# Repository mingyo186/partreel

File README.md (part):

# PartReel — open KiCad parts registry for humans & AI agents

**No login. No paywall. Machine-verified.** Every part ships as a bundle of
KiCad footprint (`.kicad_mod`) + symbol (`.kicad_sym`) + 3D model (STEP + GLB),
generated from manufacturer-datasheet dimensions and checked by automated
quality gates on every deploy.

**Site:** https://partreel.com · **API:** https://partreel.com/api/ ·
**MCP server:** `https://mcp.partreel.com/mcp` · **Agent guide:** https://partreel.com/agents/

## Why this exists

- The official KiCad library is excellent — use it when it has your part.
  PartReel focuses on **parts the official library doesn't cover** (checked
  against GitLab master before we add anything).
- Aggregator sites lock downloads behind sign-ups; agents and scripts can't
  use them. Everything here is a plain URL.
- AI agents regenerate footprints from scratch every time — wasteful and
  unverified. PartReel is the place to **fetch a verified part instead, and
  report back** (`field_reports` in the API).

## Provenance — verify us, don't trust us

Every part's API entry (`/api/v1/parts/<id>.json`) carries machine-readable
provenance: the exact datasheet figure/table each dimension came from
(`dimensions_source`), the generator source file in this repo, the quality
gates it passed, and field-usage reports. Gates run in CI on every push and
**block deployment on failure** — see [`.github/workflows/deploy.yml`](.github/workflows/deploy.yml).

| Gate | Checks |
|---|---|
| `validate_kicad.py` | s-expression structure, pads, layers, pin-1 |
| KLC drawing rules | silk 0.12 / fab 0.10 + pin-1 chamfer / courtyard 0.05 |
| `check_overlap.py` | no overlapping text in previews |
| `check_render.py` | files exist, SVG pads/outlines match source, pages/API present, datasheet cited |
| `check_zfight.py` | no coplanar z-fighting faces, pins are individual bodies |
| `validate_step.py` | STEP solids pass FreeCAD kernel isValid |

## For AI agents

- Static JSON API, no auth, no rate limit: [`/api/v1/parts.json`](https://partreel.com/api/v1/parts.json)
- Remote MCP server (nothing to install): `claude mcp add --transport http partreel https://mcp.partreel.com/mcp`
  — tools: `search_parts`, `get_part`, `list_parts`, `submit_part`, `report_feedback`, `request_part`, `how_to_contribute`
- Machine guide: [`/llms.txt`](https://partreel.com/llms.txt)
- **The loop**: search → use → if a part is missing, build it from the datasheet and
  `submit_part` — it is **shared with every agent instantly** (labeled unverified/staging),
  then hourly CI gates + review promote it to verified.
- `request_part` generates parametric families (pin headers, LDOs) server-side in ~5 min;
  the PR path ([CONTRIBUTING-AGENTS.md](CONTRIBUTING-AGENTS.md)) remains for 3D models and edits.

## Repository layout

```
library/                 part assets (CC-BY-4.0): .kicad_mod / .kicad_sym / .step / .glb / meta.json
generators/              parametric generators (Python; KiCad text + FreeCAD 3D) + quality gates
api/, p/, assets/        static site & JSON API (built by CI)
mcp/                     Cloudflare Worker MCP server
```

## License

- **Code** (generators, site): [MIT](LICENSE)
- **Part assets** (library/): [CC-BY-4.0](library/LICENSE)

Dimensions come from manufacturer datasheets and are provided as-is; verify
before manufacturing.

## Credits

Bug reports are contributions. Reporters whose feedback led to a fix are
recorded in [CREDITS.md](CREDITS.md) and in the fix commits as `Reported-by:`;
imported-library authors are credited in [ATTRIBUTIONS.md](ATTRIBUTIONS.md).

## Parts index

<!-- PARTS:BEGIN -->
Currently **18258 parts**, all machine-verified (structure, KLC drawing rules, render completeness, 3D coplanar/merged-pin checks, STEP kernel) with datasheet-cited dimensions.

### connector (4330)

| Part | MPN | Manufacturer | Files |
|---|---|---|---|
| [004500 (CERN library)](https://partreel.com/p/cern_erni_004500/) | `004500` | ERNI | [cern_erni_004500](library/connector/cern/cern_erni_004500) |
| [02 01 160 2101 (CERN library)](https://partreel.com/p/cern_harting_02_01_160_2101/) | `02 01 160 2101` | HARTING | [cern_harting_02_01_160_2101](library/connector/cern/cern_harting_02_01_160_2101) |
| [02 01 160 2102 (CERN library)](https://partreel.com/p/cern_harting_02_01_160_2102/) | `02 01 160 2102` | HARTING | [cern_harting_02_01_160_2102](library/connector/cern/cern_harting_02_01_160_2102) |
| [02 02 160 2201 (CERN library)](https://partreel.com/p/cern_harting_02_02_160_2201/) | `02 02 160 2201` | HARTING | [cern_harting_02_02_160_2201](library/connector/cern/cern_harting_02_02_160_2201) |
| [02 02 160 2301 (CERN library)](https://partreel.com/p/cern_harting_02_02_160_2301/) | `02 02 160 2301` | HARTING | [cern_harting_02_02_160_2301](library/connector/cern/cern_harting_02_02_160_2301) |
| [02 04 160 1101 (CERN library)](https://partreel.com/p/cern_harting_02_04_160_1101/) | `02 04 160 1101` | HARTING | [cern_harting_02_04_160_1101](library/connector/cern/cern_harting_02_04_160_1101) |
| [02 07 160 1101 (CERN library)](https://partreel.com/p/cern_harting_02_07_160_1101/) | `02 07 160 1101` | HARTING | [cern_harting_02_07_160_1101](library/connector/cern/cern_harting_02_07_160_1101) |
| [031-6575 (CERN library)](https://partreel.com/p/cern_amphenol_031_6575/) | `031-6575` | AMPHENOL-RF | [cern_amphenol_031_6575](library/connector/cern/cern_amphenol_031_6575) |
| [054392 (CERN library)](https://partreel.com/p/cern_erni_054392/) | `054392` | ERNI | [cern_erni_054392](library/connector/cern/cern_erni_054392) |
| [054546 (CERN library)](https://partreel.com/p/cern_erni_054546/) | `054546` | ERNI | [cern_erni_054546](library/connector/cern/cern_erni_054546) |
| [054594 (CERN library)](https://partreel.com/p/cern_erni_054594/) | `054594` | ERNI | [cern_erni_054594](library/connector/cern/cern_erni_054594) |
| [054595 (CERN library)](https://partreel.com/p/cern_erni_054595/) | `054595` | ERNI | [cern_erni_054595](library/connector/cern/cern_erni_054595) |
| [054596 (CERN library)](https://partreel.com/p/cern_erni_054596/) | `054596` | ERNI | [cern_erni_054596](library/connector/cern/cern_erni_054596) |
| [063197 (CERN library)](https://partreel.com/p/cern_erni_063197/) | `063197` | ERNI | [cern_erni_063197](library/connector/cern/cern_erni_063197) |
| [063209 (CERN library)](https://partreel.com/p/cern_erni_063209/) | `063209` | ERNI | [cern_erni_063209](library/connector/cern/cern_erni_063209) |
| [063210 (CERN library)](https://partreel.com/p/cern_erni_063210/) | `063210` | ERNI | [cern_erni_063210](library/connector/cern/cern_erni_063210) |
| [064317 (CERN library)](https://partreel.com/p/cern_erni_064317/) | `064317` | ERNI | [cern_erni_064317](library/connector/cern/cern_erni_064317) |
| [064318 (CERN library)](https://partreel.com/p/cern_erni_064318/) | `064318` | ERNI | [cern_erni_064318](library/connector/cern/cern_erni_064318) |
| [064321 (CERN library)](https://partreel.com/p/cern_erni_064321/) | `064321` | ERNI | [cern_erni_064321](library/connector/cern/cern_erni_064321) |
| [09 02 164 2921 (CERN library)](https://partreel.com/p/cern_harting_09_02_164_2921/) | `09 02 164 2921` | HARTING | [cern_harting_09_02_164_2921](library/connector/cern/cern_harting_09_02_164_2921) |
| [09 02 264 6825 (CERN library)](https://partreel.com/p/cern_harting_09_02_264_6825/) | `09 02 264 6825` | HARTING | [cern_harting_09_02_264_6825](library/connector/cern/cern_harting_09_02_264_6825) |
| [09 02 264 6850 (CERN library)](https://partreel.com/p/cern_harting_09_02_264_6850/) | `09 02 264 6850` | HARTING | [cern_harting_09_02_264_6850](library/connector/cern/cern_harting_09_02_264_6850) |
| [09 03 000 6104 (CERN library)](https://partreel.com/p/cern_harting_09_03_000_6104/) | `09 03 000 6104` | HARTING | [cern_harting_09_03_000_6104](library/connector/cern/cern_harting_09_03_000_6104) |
| [09 03 000 6110 (CERN library)](https://partreel.com/p/cern_harting_09_03_000_6110/) | `09 03 000 6110` | HARTING | [cern_harting_09_03_000_6110](library/connector/cern/cern_harting_09_03_000_6110) |
| [09 03 000 6162 (CERN library)](https://partreel.com/p/cern_harting_09_03_000_6162/) | `09 03 000 6162` | HARTING | [cern_harting_09_03_000_6162](library/connector/cern/cern_harting_09_03_000_6162) |
| [09 03 000 6182 (CERN library)](https://partreel.com/p/cern_harting_09_03_000_6182/) | `09 03 000 6182` | HARTING | [cern_harting_09_03_000_6182](library/connector/cern/cern_harting_09_03_000_6182) |
| [09 03 000 6225 (CERN library)](https://partreel.com/p/cern_harting_09_03_000_6225/) | `09 03 000 6225` | HARTING | [cern_harting_09_03_000_6225](library/connector/cern/cern_harting_09_03_000_6225) |
| [09 03 000 6262 (CERN library)](https://partreel.com/p/cern_harting_09_03_000_6262/) | `09 03 000 6262` | HARTING | [cern_harting_09_03_000_6262](library/connector/cern/cern_harting_09_03_000_6262) |
| [09 03 000 6265 (CERN library)](https://partreel.com/p/cern_harting_09_03_000_6265/) | `09 03 000 6265` | HARTING | [cern_harting_09_03_000_6265](library/connector/cern/cern_harting_09_03_000_6265) |
| [09 03 124 6901 (CERN library)](https://partreel.com/p/cern_harting_09_03_124_6901/) | `09 03 124 6901` | HARTING | [cern_harting_09_03_124_6901](library/connector/cern/cern_harting_09_03_124_6901) |
| [09 03 142 6901 (CERN library)](https://partreel.com/p/cern_harting_09_03_142_6901/) | `09 03 142 6901` | HARTING | [cern_harting_09_03_142_6901](library/connector/cern/cern_harting_09_03_142_6901) |
| [09 03 160 6901 (CERN library)](https://partreel.com/p/cern_harting_09_03_160_6901/) | `09 03 160 6901` | HARTING | [cern_harting_09_03_160_6901](library/connector/cern/cern_harting_09_03_160_6901) |
| [09 03 164 2921 (CERN library)](https://partreel.com/p/cern_harting_09_03_164_2921/) | `09 03 164 2921` | HARTING | [cern_harting_09_03_164_2921](library/connector/cern/cern_harting_09_03_164_2921) |
| [09 03 164 6921 (CERN library)](https://partreel.com/p/cern_harting_09_03_164_6921/) | `09 03 164 6921` | HARTING | [cern_harting_09_03_164_6921](library/connector/cern/cern_harting_09_03_164_6921) |
| [09 03 164 6922 (CERN library)](https://partreel.com/p/cern_harting_09_03_164_6922/) | `09 03 164 6922` | HARTING | [cern_harting_09_03_164_6922](library/connector/cern/cern_harting_09_03_164_6922) |
| [09 03 164 6951 (CERN library)](https://partreel.com/p/cern_harting_09_03_164_6951/) | `09 03 164 6951` | HARTING | [cern_harting_09_03_164_6951](library/connector/cern/cern_harting_09_03_164_6951) |
| [09 03 178 7901 (CERN library)](https://partreel.com/p/cern_harting_09_03_178_7901/) | `09 03 178 7901` | HARTING | [cern_harting_09_03_178_7901](library/connector/cern/cern_harting_09_03_178_7901) |
| [09 03 196 2921 (CERN library)](https://partreel.com/p/cern_harting_09_03_196_2921/) | `09 03 196 2921` | HARTING | [cern_harting_09_03_196_2921](library/connector/cern/cern_harting_09_03_196_2921) |
| [09 03 196 6921 (CERN library)](https://partreel.com/p/cern_harting_09_03_196_6921/) | `09 03 196 6921` | HARTING | [cern_harting_09_03_196_6921](library/connector/cern/cern_harting_09_03_196_6921) |
| [09 03 224 6805 (CERN library)](https://partreel.com/p/cern_harting_09_03_224_6805/) | `09 03 224 6805` | HARTING | [cern_harting_09_03_224_6805](library/connector/cern/cern_harting_09_03_224_6805) |
| [09 03 224 6830 (CERN library)](https://partreel.com/p/cern_harting_09_03_224_6830/) | `09 03 224 6830` | HARTING | [cern_harting_09_03_224_6830](library/connector/cern/cern_harting_09_03_224_6830) |
| [09 03 224 6864 (CERN library)](https://partreel.com/p/cern_harting_09_03_224_6864/) | `09 03 224 6864` | HARTING | [cern_harting_09_03_224_6864](library/connector/cern/cern_harting_09_03_224_6864) |
| [09 03 224 6864 (CERN library)](https://partreel.com/p/cern_harting_09_03_224_6864_a/) | `09 03 224 6864` | HARTING | [cern_harting_09_03_224_6864_a](library/connector/cern/cern_harting_09_03_224_6864_a) |
| [09 03 232 6825 (CERN library)](https://partreel.com/p/cern_harting_09_03_232_6825/) | `09 03 232 6825` | HARTING | [cern_harting_09_03_232_6825](library/connector/cern/cern_harting_09_03_232_6825) |
| [09 03 232 6850 (CERN library)](https://partreel.com/p/cern_harting_09_03_232_6850/) | `09 03 232 6850` | HARTING | [cern_harting_09_03_232_6850](library/connector/cern/cern_harting_09_03_232_6850) |
| [09 03 242 6805 (CERN library)](https://partreel.com/p/cern_harting_09_03_242_6805/) | `09 03 242 6805` | HARTING | [cern_harting_09_03_242_6805](library/connector/cern/cern_harting_09_03_242_6805) |
| [09 03 242 6805 (CERN library)](https://partreel.com/p/cern_harting_09_03_242_6805_a/) | `09 03 242 6805` | HARTING | [cern_harting_09_03_242_6805_a](library/connector/cern/cern_harting_09_03_242_6805_a) |
| [09 03 260 6804 (CERN library)](https://partreel.com/p/cern_harting_09_03_260_6804/) | `09 03 260 6804` | HARTING | [cern_harting_09_03_260_6804](library/connector/cern/cern_harting_09_03_260_6804) |
| [09 03 264 6825 (CERN library)](https://partreel.com/p/cern_harting_09_03_264_6825/) | `09 03 264 6825` | HARTING | [cern_harting_09_03_264_6825](library/connector/cern/cern_harting_09_03_264_6825) |
| [09 03 264 6850 (CERN library)](https://partreel.com/p/cern_harting_09_03_264_6850/) | `09 03 264 6850` | HARTING | [cern_harting_09_03_264_6850](library/connector/cern/cern_harting_09_03_264_6850) |
| [09 03 278 6804 (CERN library)](https://partreel.com/p/cern_harting_09_03_278_6804/) | `09 03 278 6804` | HARTING | [cern_harting_09_03_278_6804](library/connector/cern/cern_harting_09_03_278_6804) |
| [09 03 296 2825 (CERN library)](https://partreel.com/p/cern_harting_09_03_296_2825/) | `09 03 296 2825` | HARTING | [cern_harting_09_03_296_2825](library/connector/cern/cern_harting_09_03_296_2825) |
| [09 03 296 2850 (CERN library)](https://partreel.com/p/cern_harting_09_03_296_2850/) | `09 03 296 2850` | HARTING | [cern_harting_09_03_296_2850](library/connector/cern/cern_harting_09_03_296_2850) |
| [09 03 296 6824 (CERN library)](https://partreel.com/p/cern_harting_09_03_296_6824/) | `09 03 296 6824` | HARTING | [cern_harting_09_03_296_6824](library/connector/cern/cern_harting_09_03_296_6824) |
| [09 03 296 6825 (CERN library)](https://partreel.com/p/cern_harting_09_03_296_6825/) | `09 03 296 6825` | HARTING | [cern_harting_09_03_296_6825](library/connector/cern/cern_harting_09_03_296_6825) |
| [09 03 296 6850 (CERN library)](https://partreel.com/p/cern_harting_09_03_296_6850/) | `09 03 296 6850` | HARTING | [cern_harting_09_03_296_6850](library/connector/cern/cern_harting_09_03_296_6850) |
| [09 03 296 6861 (CERN library)](https://partreel.com/p/cern_harting_09_03_296_6861/) | `09 03 296 6861` | HARTING | [cern_harting_09_03_296_6861](library/connector/cern/cern_harting_09_03_296_6861) |
| [09 03 478 6864 (CERN library)](https://partreel.com/p/cern_harting_09_03_478_6864/) | `09 03 478 6864` | HARTING | [cern_harting_09_03_478_6864](library/connector/cern/cern_harting_09_03_478_6864) |
| [09 03 696 6921 (CERN library)](https://partreel.com/p/cern_harting_09_03_696_6921/) | `09 03 696 6921` | HARTING | [cern_harting_09_03_696_6921](library/connector/cern/cern_harting_09_03_696_6921) |
| [09 03 796 6825 (CERN library)](https://partreel.com/p/cern_harting_09_03_796_6825/) | `09 03 796 6825` | HARTING | [cern_harting_09_03_796_6825](library/connector/cern/cern_harting_09_03_796_6825) |
| [09 03 796 6850 (CERN library)](https://partreel.com/p/cern_harting_09_03_796_6850/) | `09 03 796 6850` | HARTING | [cern_harting_09_03_796_6850](library/connector/cern/cern_harting_09_03_796_6850) |
| [09 04 132 2921 (CERN library)](https://partreel.com/p/cern_harting_09_04_132_2921/) | `09 04 132 2921` | HARTING | [cern_harting_09_04_132_2921](library/connector/cern/cern_harting_09_04_132_2921) |
| [09 04 132 6921 (CERN library)](https://partreel.com/p/cern_harting_09_04_132_6921/) | `09 04 132 6921` | HARTING | [cern_harting_09_04_132_6921](library/connector/cern/cern_harting_09_04_132_6921) |
| [09 04 232 6826 (CERN library)](https://partreel.com/p/cern_harting_09_04_232_6826/) | `09 04 232 6826` | HARTING | [cern_harting_09_04_232_6826](library/connector/cern/cern_harting_09_04_232_6826) |
| [09 04 232 6831 (CERN library)](https://partreel.com/p/cern_harting_09_04_232_6831/) | `09 04 232 6831` | HARTING | [cern_harting_09_04_232_6831](library/connector/cern/cern_harting_09_04_232_6831) |
| [09 05 148 2931 (CERN library)](https://partreel.com/p/cern_harting_09_05_148_2931/) | `09 05 148 2931` | HARTING | [cern_harting_09_05_148_2931](library/connector/cern/cern_harting_09_05_148_2931) |
| [09 05 248 6831 (CERN library)](https://partreel.com/p/cern_harting_09_05_248_6831/) | `09 05 248 6831` | HARTING | [cern_harting_09_05_248_6831](library/connector/cern/cern_harting_09_05_248_6831) |
| [09 06 031 2921 (CERN library)](https://partreel.com/p/cern_harting_09_06_031_2921/) | `09 06 031 2921` | HARTING | [cern_harting_09_06_031_2921](library/connector/cern/cern_harting_09_06_031_2921) |
| [09 06 048 2905 (CERN library)](https://partreel.com/p/cern_harting_09_06_048_2905/) | `09 06 048 2905` | HARTING | [cern_harting_09_06_048_2905](library/connector/cern/cern_harting_09_06_048_2905) |
| [09 06 115 2911 (CERN library)](https://partreel.com/p/cern_harting_09_06_115_2911/) | `09 06 115 2911` | HARTING | [cern_harting_09_06_115_2911](library/connector/cern/cern_harting_09_06_115_2911) |
| [09 06 131 6922 (CERN library)](https://partreel.com/p/cern_harting_09_06_131_6922/) | `09 06 131 6922` | HARTING | [cern_harting_09_06_131_6922](library/connector/cern/cern_harting_09_06_131_6922) |
| [09 06 131 6924 (CERN library)](https://partreel.com/p/cern_harting_09_06_131_6924/) | `09 06 131 6924` | HARTING | [cern_harting_09_06_131_6924](library/connector/cern/cern_harting_09_06_131_6924) |
| [09 06 132 6931 (CERN library)](https://partreel.com/p/cern_harting_09_06_132_6931/) | `09 06 132 6931` | HARTING | [cern_harting_09_06_132_6931](library/connector/cern/cern_harting_09_06_132_6931) |
| [09 06 148 2901 222 (CERN library)](https://partreel.com/p/cern_harting_09_06_148_2901_222/) | `09 06 148 2901 222` | HARTING | [cern_harting_09_06_148_2901_222](library/connector/cern/cern_harting_09_06_148_2901_222) |
| [09 06 148 6901 (CERN library)](https://partreel.com/p/cern_harting_09_06_148_6901/) | `09 06 148 6901` | HARTING | [cern_harting_09_06_148_6901](library/connector/cern/cern_harting_09_06_148_6901) |
| [09 06 203 2811 (CERN library)](https://partreel.com/p/cern_harting_09_06_203_2811/) | `09 06 203 2811` | HARTING | [cern_harting_09_06_203_2811](library/connector/cern/cern_harting_09_06_203_2811) |
| [09 06 215 2811 (CERN library)](https://partreel.com/p/cern_harting_09_06_215_2811/) | `09 06 215 2811` | HARTING | [cern_harting_09_06_215_2811](library/connector/cern/cern_harting_09_06_215_2811) |
| [09 06 215 2821 (CERN library)](https://partreel.com/p/cern_harting_09_06_215_2821/) | `09 06 215 2821` | HARTING | [cern_harting_09_06_215_2821](library/connector/cern/cern_harting_09_06_215_2821) |
| [09 06 215 2854 (CERN library)](https://partreel.com/p/cern_harting_09_06_215_2854/) | `09 06 215 2854` | HARTING | [cern_harting_09_06_215_2854](library/connector/cern/cern_harting_09_06_215_2854) |
| [09 06 215 2856 (CERN library)](https://partreel.com/p/cern_harting_09_06_215_2856/) | `09 06 215 2856` | HARTING | [cern_harting_09_06_215_2856](library/connector/cern/cern_harting_09_06_215_2856) |
| [09 06 231 2881 (CERN library)](https://partreel.com/p/cern_harting_09_06_231_2881/) | `09 06 231 2881` | HARTING | [cern_harting_09_06_231_2881](library/connector/cern/cern_harting_09_06_231_2881) |
| [09 06 231 6822 (CERN library)](https://partreel.com/p/cern_harting_09_06_231_6822/) | `09 06 231 6822` | HARTING | [cern_harting_09_06_231_6822](library/connector/cern/cern_harting_09_06_231_6822) |
| [09 06 231 6822 (CERN library)](https://partreel.com/p/cern_harting_09_06_231_6822_a/) | `09 06 231 6822` | HARTING | [cern_harting_09_06_231_6822_a](library/connector/cern/cern_harting_09_06_231_6822_a) |
| [09 06 248 6826 (CERN library)](https://partreel.com/p/cern_harting_09_06_248_6826/) | `09 06 248 6826` | HARTING | [cern_harting_09_06_248_6826](library/connector/cern/cern_harting_09_06_248_6826) |
| [09 06 248 6832 (CERN library)](https://partreel.com/p/cern_harting_09_06_248_6832/) | `09 06 248 6832` | HARTING | [cern_harting_09_06_248_6832](library/connector/cern/cern_harting_09_06_248_6832) |
| [09 06 248 6834 (CERN library)](https://partreel.com/p/cern_harting_09_06_248_6834/) | `09 06 248 6834` | HARTING | [cern_harting_09_06_248_6834](library/connector/cern/cern_harting_09_06_248_6834) |
| [09 06 248 6836 (CERN library)](https://partreel.com/p/cern_harting_09_06_248_6836/) | `09 06 248 6836` | HARTING | [cern_harting_09_06_248_6836](library/connector/cern/cern_harting_09_06_248_6836) |
| [09 06 248 7833 (CERN library)](https://partreel.com/p/cern_harting_09_06_248_7833/) | `09 06 248 7833` | HARTING | [cern_harting_09_06_248_7833](library/connector/cern/cern_harting_09_06_248_7833) |
| [09 12 000 9905 (CERN library)](https://partreel.com/p/cern_harting_09_12_000_9905/) | `09 12 000 9905` | HARTING | [cern_harting_09_12_000_9905](library/connector/cern/cern_harting_09_12_000_9905) |
| [09 12 000 9905 (CERN library)](https://partreel.com/p/cern_harting_09_12_000_9905_alt/) | `09 12 000 9905` | HARTING | [cern_harting_09_12_000_9905_alt](library/connector/cern/cern_harting_09_12_000_9905_alt) |
| [09 12 000 9908 (CERN library)](https://partreel.com/p/cern_harting_09_12_000_9908/) | `09 12 000 9908` | HARTING | [cern_harting_09_12_000_9908](library/connector/cern/cern_harting_09_12_000_9908) |
| [09 12 012 9901 (CERN library)](https://partreel.com/p/cern_harting_09_12_012_9901/) | `09 12 012 9901` | HARTING | [cern_harting_09_12_012_9901](library/connector/cern/cern_harting_09_12_012_9901) |
| [09 16 000 9908 (CERN library)](https://partreel.com/p/cern_harting_09_16_000_9908/) | `09 16 000 9908` | HARTING | [cern_harting_09_16_000_9908](library/connector/cern/cern_harting_09_16_000_9908) |
| [09 16 000 9918 (CERN library)](https://partreel.com/p/cern_harting_09_16_000_9918/) | `09 16 000 9918` | HARTING | [cern_harting_09_16_000_9918](library/connector/cern/cern_harting_09_16_000_9918) |
| [09 16 000 9918 (CERN library)](https://partreel.com/p/cern_harting_09_16_000_9918_alt/) | `09 16 000 9918` | HARTING | [cern_harting_09_16_000_9918_alt](library/connector/cern/cern_harting_09_16_000_9918_alt) |
| [09 18 516 6324 (CERN library)](https://partreel.com/p/cern_harting_09_18_516_6324/) | `09 18 516 6324` | HARTING | [cern_harting_09_18_516_6324](library/connector/cern/cern_harting_09_18_516_6324) |
| [09 18 516 6324 (CERN library)](https://partreel.com/p/cern_harting_09_18_516_6324_alt/) | `09 18 516 6324` | HARTING | [cern_harting_09_18_516_6324_alt](library/connector/cern/cern_harting_09_18_516_6324_alt) |
| [09 19 564 6824 (CERN library)](https://partreel.com/p/cern_harting_09_19_564_6824/) | `09 19 564 6824` | HARTING | [cern_harting_09_19_564_6824](library/connector/cern/cern_harting_09_19_564_6824) |
| [09 19 564 6824 (CERN library)](https://partreel.com/p/cern_harting_09_19_564_6824_alt/) | `09 19 564 6824` | HARTING | [cern_harting_09_19_564_6824_alt](library/connector/cern/cern_harting_09_19_564_6824_alt) |
| [09 22 116 6921 (CERN library)](https://partreel.com/p/cern_harting_09_22_116_6921/) | `09 22 116 6921` | HARTING | [cern_harting_09_22_116_6921](library/connector/cern/cern_harting_09_22_116_6921) |
| [09 22 132 6921 (CERN library)](https://partreel.com/p/cern_harting_09_22_132_6921/) | `09 22 132 6921` | HARTING | [cern_harting_09_22_132_6921](library/connector/cern/cern_harting_09_22_132_6921) |
| [09 22 232 6825 (CERN library)](https://partreel.com/p/cern_harting_09_22_232_6825/) | `09 22 232 6825` | HARTING | [cern_harting_09_22_232_6825](library/connector/cern/cern_harting_09_22_232_6825) |
| [09 22 232 6850 (CERN library)](https://partreel.com/p/cern_harting_09_22_232_6850/) | `09 22 232 6850` | HARTING | [cern_harting_09_22_232_6850](library/connector/cern/cern_harting_09_22_232_6850) |
| [09 23 116 6931 (CERN library)](https://partreel.com/p/cern_harting_09_23_116_6931/) | `09 23 116 6931` | HARTING | [cern_harting_09_23_116_6931](library/connector/cern/cern_harting_09_23_116_6931) |
| [09 23 116 6931 (CERN library)](https://partreel.com/p/cern_harting_09_23_116_6931_alt/) | `09 23 116 6931` | HARTING | [cern_harting_09_23_116_6931_alt](library/connector/cern/cern_harting_09_23_116_6931_alt) |
| [09 23 132 7921 (CERN library)](https://partreel.com/p/cern_harting_09_23_132_7921/) | `09 23 132 7921` | HARTING | [cern_harting_09_23_132_7921](library/connector/cern/cern_harting_09_23_132_7921) |
| [09 23 148 6921 (CERN library)](https://partreel.com/p/cern_harting_09_23_148_6921/) | `09 23 148 6921` | HARTING | [cern_harting_09_23_148_6921](library/connector/cern/cern_harting_09_23_148_6921) |
| [09 23 148 6951 (CERN library)](https://partreel.com/p/cern_harting_09_23_148_6951/) | `09 23 148 6951` | HARTING | [cern_harting_09_23_148_6951](library/connector/cern/cern_harting_09_23_148_6951) |
| [09 23 248 6824 (CERN library)](https://partreel.com/p/cern_harting_09_23_248_6824/) | `09 23 248 6824` | HARTING | [cern_harting_09_23_248_6824](library/connector/cern/cern_harting_09_23_248_6824) |
| [09 23 248 6850 (CERN library)](https://partreel.com/p/cern_harting_09_23_248_6850/) | `09 23 248 6850` | HARTING | [cern_harting_09_23_248_6850](library/connector/cern/cern_harting_09_23_248_6850) |
| [09 23 248 6866 (CERN library)](https://partreel.com/p/cern_harting_09_23_248_6866/) | `09 23 248 6866` | HARTING | [cern_harting_09_23_248_6866](library/connector/cern/cern_harting_09_23_248_6866) |
| [09 25 120 6921 (CERN library)](https://partreel.com/p/cern_harting_09_25_120_6921/) | `09 25 120 6921` | HARTING | [cern_harting_09_25_120_6921](library/connector/cern/cern_harting_09_25_120_6921) |
| [09 25 130 6921 (CERN library)](https://partreel.com/p/cern_harting_09_25_130_6921/) | `09 25 130 6921` | HARTING | [cern_harting_09_25_130_6921](library/connector/cern/cern_harting_09_25_130_6921) |
| [09 25 130 6922 (CERN library)](https://partreel.com/p/cern_harting_09_25_130_6922/) | `09 25 130 6922` | HARTING | [cern_harting_09_25_130_6922](library/connector/cern/cern_harting_09_25_130_6922) |
| [09 25 230 6824 (CERN library)](https://partreel.com/p/cern_harting_09_25_230_6824/) | `09 25 230 6824` | HARTING | [cern_harting_09_25_230_6824](library/connector/cern/cern_harting_09_25_230_6824) |
| [09 25 230 6850 (CERN library)](https://partreel.com/p/cern_harting_09_25_230_6850/) | `09 25 230 6850` | HARTING | [cern_harting_09_25_230_6850](library/connector/cern/cern_harting_09_25_230_6850) |
| [09 28 148 6519 (CERN library)](https://partreel.com/p/cern_harting_09_28_148_6519/) | `09 28 148 6519` | HARTING | [cern_harting_09_28_148_6519](library/connector/cern/cern_harting_09_28_148_6519) |
| [09 28 148 6902 (CERN library)](https://partreel.com/p/cern_harting_09_28_148_6902/) | `09 28 148 6902` | HARTING | [cern_harting_09_28_148_6902](library/connector/cern/cern_harting_09_28_148_6902) |
| [09 28 248 6801 (CERN library)](https://partreel.com/p/cern_harting_09_28_248_6801/) | `09 28 248 6801` | HARTING | [cern_harting_09_28_248_6801](library/connector/cern/cern_harting_09_28_248_6801) |
| [09 29 130 6904 (CERN library)](https://partreel.com/p/cern_harting_09_29_130_6904/) | `09 29 130 6904` | HARTING | [cern_harting_09_29_130_6904](library/connector/cern/cern_harting_09_29_130_6904) |
| [09 29 130 6904 (CERN library)](https://partreel.com/p/cern_harting_09_29_130_6904_reverse/) | `09 29 130 6904` | HARTING | [cern_harting_09_29_130_6904_reverse](library/connector/cern/cern_harting_09_29_130_6904_reverse) |
| [09 32 000 6295 (CERN library)](https://partreel.com/p/cern_harting_09_32_000_6295/) | `09 32 000 6295` | HARTING | [cern_harting_09_32_000_6295](library/connector/cern/cern_harting_09_32_000_6295) |
| [09 32 000 6295 (CERN library)](https://partreel.com/p/cern_harting_09_32_000_6295_alt/) | `09 32 000 6295` | HARTING | [cern_harting_09_32_000_6295_alt](library/connector/cern/cern_harting_09_32_000_6295_alt) |
| [09 33 000 9811 (CERN library)](https://partreel.com/p/cern_harting_09_33_000_9811/) | `09 33 000 9811` | HARTING | [cern_harting_09_33_000_9811](library/connector/cern/cern_harting_09_33_000_9811) |
| [09 33 000 9812 (CERN library)](https://partreel.com/p/cern_harting_09_33_000_9812/) | `09 33 000 9812` | HARTING | [cern_harting_09_33_000_9812](library/connector/cern/cern_harting_09_33_000_9812) |
| [09 33 000 9812 (CERN library)](https://partreel.com/p/cern_harting_09_33_000_9812_a/) | `09 33 000 9812` | HARTING | [cern_harting_09_33_000_9812_a](library/connector/cern/cern_harting_09_33_000_9812_a) |
| [09 33 000 9813 (CERN library)](https://partreel.com/p/cern_harting_09_33_000_9813/) | `09 33 000 9813` | HARTING | [cern_harting_09_33_000_9813](library/connector/cern/cern_harting_09_33_000_9813) |
| [09 33 000 9815 (CERN library)](https://partreel.com/p/cern_harting_09_33_000_9815/) | `09 33 000 9815` | HARTING | [cern_harting_09_33_000_9815](library/connector/cern/cern_harting_09_33_000_9815) |
| [09 33 000 9815 (CERN library)](https://partreel.com/p/cern_harting_09_33_000_9815_a/) | `09 33 000 9815` | HARTING | [cern_harting_09_33_000_9815_a](library/connector/cern/cern_harting_09_33_000_9815_a) |
| [09 33 000 9870 (CERN library)](https://partreel.com/p/cern_harting_09_33_000_9870/) | `09 33 000 9870` | HARTING | [cern_harting_09_33_000_9870](library/connector/cern/cern_harting_09_33_000_9870) |
| [09 33 000 9870 (CERN library)](https://partreel.com/p/cern_harting_09_33_000_9870_alt/) | `09 33 000 9870` | HARTING | [cern_harting_09_33_000_9870_alt](library/connector/cern/cern_harting_09_33_000_9870_alt) |
| [09 33 000 9871 (CERN library)](https://partreel.com/p/cern_harting_09_33_000_9871/) | `09 33 000 9871` | HARTING | [cern_harting_09_33_000_9871](library/connector/cern/cern_harting_09_33_000_9871) |
| [09 33 000 9871 (CERN library)](https://partreel.com/p/cern_harting_09_33_000_9871_alt/) | `09 33 000 9871` | HARTING | [cern_harting_09_33_000_9871_alt](library/connector/cern/cern_harting_09_33_000_9871_alt) |
| [09 33 000 9872 (CERN library)](https://partreel.com/p/cern_harting_09_33_000_9872/) | `09 33 000 9872` | HARTING | [cern_harting_09_33_000_9872](library/connector/cern/cern_harting_09_33_000_9872) |
| [09 33 000 9872 (CERN library)](https://partreel.com/p/cern_harting_09_33_000_9872_alt/) | `09 33 000 9872` | HARTING | [cern_harting_09_33_000_9872_alt](library/connector/cern/cern_harting_09_33_000_9872_alt) |
| [09 33 000 9873 (CERN library)](https://partreel.com/p/cern_harting_09_33_000_9873/) | `09 33 000 9873` | HARTING | [cern_harting_09_33_000_9873](library/connector/cern/cern_harting_09_33_000_9873) |
| [09 33 000 9880 (CERN library)](https://partreel.com/p/cern_harting_09_33_000_9880/) | `09 33 000 9880` | HARTING | [cern_harting_09_33_000_9880](library/connector/cern/cern_harting_09_33_000_9880) |
| [09 33 000 9880 (CERN library)](https://partreel.com/p/cern_harting_09_33_000_9880_alt/) | `09 33 000 9880` | HARTING | [cern_harting_09_33_000_9880_alt](library/connector/cern/cern_harting_09_33_000_9880_alt) |
| [09 33 000 9996 (CERN library)](https://partreel.com/p/cern_harting_09_33_000_9996/) | `09 33 000 9996` | HARTING | [cern_harting_09_33_000_9996](library/connector/cern/cern_harting_09_33_000_9996) |
| [09 45 281 2800 (CERN library)](https://partreel.com/p/cern_harting_09_45_281_2800/) | `09 45 281 2800` | HARTING | [cern_harting_09_45_281_2800](library/connector/cern/cern_harting_09_45_281_2800) |
| [09 45 281 2810 (CERN library)](https://partreel.com/p/cern_harting_09_45_281_2810/) | `09 45 281 2810` | HARTING | [cern_harting_09_45_281_2810](library/connector/cern/cern_harting_09_45_281_2810) |
| [09 46 500 3400 (CERN library)](https://partreel.com/p/cern_harting_09_46_500_3400/) | `09 46 500 3400` | HARTING | [cern_harting_09_46_500_3400](library/connector/cern/cern_harting_09_46_500_3400) |
| [09 46 500 4400 (CERN library)](https://partreel.com/p/cern_harting_09_46_500_4400/) | `09 46 500 4400` | HARTING | [cern_harting_09_46_500_4400](library/connector/cern/cern_harting_09_46_500_4400) |
| [09 46 500 4400 (CERN library)](https://partreel.com/p/cern_harting_09_46_500_4400_alt/) | `09 46 500 4400` | HARTING | [cern_harting_09_46_500_4400_alt](library/connector/cern/cern_harting_09_46_500_4400_alt) |
| [09 55 315 6612 741 (CERN library)](https://partreel.com/p/cern_harting_09_55_315_6612_741/) | `09 55 315 6612 741` | HARTING | [cern_harting_09_55_315_6612_741](library/connector/cern/cern_harting_09_55_315_6612_741) |
| [09 55 315 6612 741 (CERN library)](https://partreel.com/p/cern_harting_09_55_315_6612_741_alt/) | `09 55 315 6612 741` | HARTING | [cern_harting_09_55_315_6612_741_alt](library/connector/cern/cern_harting_09_55_315_6612_741_alt) |
| [09 56 151 5513 (CERN library)](https://partreel.com/p/cern_harting_09_56_151_5513/) | `09 56 151 5513` | HARTING | [cern_harting_09_56_151_5513](library/connector/cern/cern_harting_09_56_151_5513) |
| [09 56 151 5513 (CERN library)](https://partreel.com/p/cern_harting_09_56_151_5513_alt/) | `09 56 151 5513` | HARTING | [cern_harting_09_56_151_5513_alt](library/connector/cern/cern_harting_09_56_151_5513_alt) |
| [09 56 251 5512 (CERN library)](https://partreel.com/p/cern_harting_09_56_251_5512/) | `09 56 251 5512` | HARTING | [cern_harting_09_56_251_5512](library/connector/cern/cern_harting_09_56_251_5512) |
| [09 56 251 5512 (CERN library)](https://partreel.com/p/cern_harting_09_56_251_5512_alt/) | `09 56 251 5512` | HARTING | [cern_harting_09_56_251_5512_alt](library/connector/cern/cern_harting_09_56_251_5512_alt) |
| [09 56 251 7512 (CERN library)](https://partreel.com/p/cern_harting_09_56_251_7512/) | `09 56 251 7512` | HARTING | [cern_harting_09_56_251_7512](library/connector/cern/cern_harting_09_56_251_7512) |
| [09 56 251 7512 (CERN library)](https://partreel.com/p/cern_harting_09_56_251_7512_alt/) | `09 56 251 7512` | HARTING | [cern_harting_09_56_251_7512_alt](library/connector/cern/cern_harting_09_56_251_7512_alt) |
| [09 56 262 7812 (CERN library)](https://partreel.com/p/cern_harting_09_56_262_7812/) | `09 56 262 7812` | HARTING | [cern_harting_09_56_262_7812](library/connector/cern/cern_harting_09_56_262_7812) |
| [09 56 262 7812 (CERN library)](https://partreel.com/p/cern_harting_09_56_262_7812_alt/) | `09 56 262 7812` | HARTING | [cern_harting_09_56_262_7812_alt](library/connector/cern/cern_harting_09_56_262_7812_alt) |
| [09 56 351 5513 (CERN library)](https://partreel.com/p/cern_harting_09_56_351_5513/) | `09 56 351 5513` | HARTING | [cern_harting_09_56_351_5513](library/connector/cern/cern_harting_09_56_351_5513) |
| [09 56 351 5513 (CERN library)](https://partreel.com/p/cern_harting_09_56_351_5513_alt/) | `09 56 351 5513` | HARTING | [cern_harting_09_56_351_5513_alt](library/connector/cern/cern_harting_09_56_351_5513_alt) |
| [09 56 451 5512 (CERN library)](https://partreel.com/p/cern_harting_09_56_451_5512/) | `09 56 451 5512` | HARTING | [cern_harting_09_56_451_5512](library/connector/cern/cern_harting_09_56_451_5512) |
| [09 56 451 5512 (CERN library)](https://partreel.com/p/cern_harting_09_56_451_5512_alt/) | `09 56 451 5512` | HARTING | [cern_harting_09_56_451_5512_alt](library/connector/cern/cern_harting_09_56_451_5512_alt) |
| [09 56 461 5712 (CERN library)](https://partreel.com/p/cern_harting_09_56_461_5712/) | `09 56 461 5712` | HARTING | [cern_harting_09_56_461_5712](library/connector/cern/cern_harting_09_56_461_5712) |
| [09 56 461 5712 (CERN library)](https://partreel.com/p/cern_harting_09_56_461_5712_alt/) | `09 56 461 5712` | HARTING | [cern_harting_09_56_461_5712_alt](library/connector/cern/cern_harting_09_56_461_5712_alt) |
| [09 56 551 5512 (CERN library)](https://partreel.com/p/cern_harting_09_56_551_5512/) | `09 56 551 5512` | HARTING | [cern_harting_09_56_551_5512](library/connector/cern/cern_harting_09_56_551_5512) |
| [09 56 551 5512 (CERN library)](https://partreel.com/p/cern_harting_09_56_551_5512_alt/) | `09 56 551 5512` | HARTING | [cern_harting_09_56_551_5512_alt](library/connector/cern/cern_harting_09_56_551_5512_alt) |
| [09 56 551 7513 (CERN library)](https://partreel.com/p/cern_harting_09_56_551_7513/) | `09 56 551 7513` | HARTING | [cern_harting_09_56_551_7513](library/connector/cern/cern_harting_09_56_551_7513) |
| [09 56 551 7513 (CERN library)](https://partreel.com/p/cern_harting_09_56_551_7513_alt/) | `09 56 551 7513` | HARTING | [cern_harting_09_56_551_7513_alt](library/connector/cern/cern_harting_09_56_551_7513_alt) |
| [09 56 552 7613 (CERN library)](https://partreel.com/p/cern_harting_09_56_552_7613/) | `09 56 552 7613` | HARTING | [cern_harting_09_56_552_7613](library/connector/cern/cern_harting_09_56_552_7613) |
| [09 56 552 7613 (CERN library)](https://partreel.com/p/cern_harting_09_56_552_7613_alt/) | `09 56 552 7613` | HARTING | [cern_harting_09_56_552_7613_alt](library/connector/cern/cern_harting_09_56_552_7613_alt) |
| [09 56 561 7713 (CERN library)](https://partreel.com/p/cern_harting_09_56_561_7713/) | `09 56 561 7713` | HARTING | [cern_harting_09_56_561_7713](library/connector/cern/cern_harting_09_56_561_7713) |
| [09 56 561 7713 (CERN library)](https://partreel.com/p/cern_harting_09_56_561_7713_alt/) | `09 56 561 7713` | HARTING | [cern_harting_09_56_561_7713_alt](library/connector/cern/cern_harting_09_56_561_7713_alt) |
| [09 56 562 7813 (CERN library)](https://partreel.com/p/cern_harting_09_56_562_7813/) | `09 56 562 7813` | HARTING | [cern_harting_09_56_562_7813](library/connector/cern/cern_harting_09_56_562_7813) |
| [09 56 562 7813 (CERN library)](https://partreel.com/p/cern_harting_09_56_562_7813_alt/) | `09 56 562 7813` | HARTING | [cern_harting_09_56_562_7813_alt](library/connector/cern/cern_harting_09_56_562_7813_alt) |
| [09 65 162 6811 (CERN library)](https://partreel.com/p/cern_harting_09_65_162_6811/) | `09 65 162 6811` | HARTING | [cern_harting_09_65_162_6811](library/connector/cern/cern_harting_09_65_162_6811) |
| [09 65 162 6811 (CERN library)](https://partreel.com/p/cern_harting_09_65_162_6811_alt/) | `09 65 162 6811` | HARTING | [cern_harting_09_65_162_6811_alt](library/connector/cern/cern_harting_09_65_162_6811_alt) |
| [09 65 162 6812 (CERN library)](https://partreel.com/p/cern_harting_09_65_162_6812/) | `09 65 162 6812` | HARTING | [cern_harting_09_65_162_6812](library/connector/cern/cern_harting_09_65_162_6812) |
| [09 65 162 6812 (CERN library)](https://partreel.com/p/cern_harting_09_65_162_6812_alt/) | `09 65 162 6812` | HARTING | [cern_harting_09_65_162_6812_alt](library/connector/cern/cern_harting_09_65_162_6812_alt) |
| [09 65 262 6812 (CERN library)](https://partreel.com/p/cern_harting_09_65_262_6812/) | `09 65 262 6812` | HARTING | [cern_harting_09_65_262_6812](library/connector/cern/cern_harting_09_65_262_6812) |
| [09 65 262 6812 (CERN library)](https://partreel.com/p/cern_harting_09_65_262_6812_alt/) | `09 65 262 6812` | HARTING | [cern_harting_09_65_262_6812_alt](library/connector/cern/cern_harting_09_65_262_6812_alt) |
| [09 65 321 7701 (CERN library)](https://partreel.com/p/cern_harting_09_65_321_7701/) | `09 65 321 7701` | HARTING | [cern_harting_09_65_321_7701](library/connector/cern/cern_harting_09_65_321_7701) |
| [09 65 321 7701 (CERN library)](https://partreel.com/p/cern_harting_09_65_321_7701_alt/) | `09 65 321 7701` | HARTING | [cern_harting_09_65_321_7701_alt](library/connector/cern/cern_harting_09_65_321_7701_alt) |
| [09 65 361 6712 (CERN library)](https://partreel.com/p/cern_harting_09_65_361_6712/) | `09 65 361 6712` | HARTING | [cern_harting_09_65_361_6712](library/connector/cern/cern_harting_09_65_361_6712) |
| [09 65 361 6712 (CERN library)](https://partreel.com/p/cern_harting_09_65_361_6712_alt/) | `09 65 361 6712` | HARTING | [cern_harting_09_65_361_6712_alt](library/connector/cern/cern_harting_09_65_361_6712_alt) |
| [09 65 362 6812 (CERN library)](https://partreel.com/p/cern_harting_09_65_362_6812/) | `09 65 362 6812` | HARTING | [cern_harting_09_65_362_6812](library/connector/cern/cern_harting_09_65_362_6812) |
| [09 65 362 6812 (CERN library)](https://partreel.com/p/cern_harting_09_65_362_6812_alt/) | `09 65 362 6812` | HARTING | [cern_harting_09_65_362_6812_alt](library/connector/cern/cern_harting_09_65_362_6812_alt) |
| [09 65 421 7702 (CERN library)](https://partreel.com/p/cern_harting_09_65_421_7702/) | `09 65 421 7702` | HARTING | [cern_harting_09_65_421_7702](library/connector/cern/cern_harting_09_65_421_7702) |
| [09 65 421 7702 (CERN library)](https://partreel.com/p/cern_harting_09_65_421_7702_alt/) | `09 65 421 7702` | HARTING | [cern_harting_09_65_421_7702_alt](library/connector/cern/cern_harting_09_65_421_7702_alt) |
| [09 65 462 6812 (CERN library)](https://partreel.com/p/cern_harting_09_65_462_6812/) | `09 65 462 6812` | HARTING | [cern_harting_09_65_462_6812](library/connector/cern/cern_harting_09_65_462_6812) |
| [09 65 462 6812 (CERN library)](https://partreel.com/p/cern_harting_09_65_462_6812_alt/) | `09 65 462 6812` | HARTING | [cern_harting_09_65_462_6812_alt](library/connector/cern/cern_harting_09_65_462_6812_alt) |
| [09 66 111 7501 (CERN library)](https://partreel.com/p/cern_harting_09_66_111_7501/) | `09 66 111 7501` | HARTING | [cern_harting_09_66_111_7501](library/connector/cern/cern_harting_09_66_111_7501) |
| [09 66 111 7501 (CERN library)](https://partreel.com/p/cern_harting_09_66_111_7501_alt/) | `09 66 111 7501` | HARTING | [cern_harting_09_66_111_7501_alt](library/connector/cern/cern_harting_09_66_111_7501_alt) |
| [09 66 111 7502 (CERN library)](https://partreel.com/p/cern_harting_09_66_111_7502/) | `09 66 111 7502` | HARTING | [cern_harting_09_66_111_7502](library/connector/cern/cern_harting_09_66_111_7502) |
| [09 66 111 7502 (CERN library)](https://partreel.com/p/cern_harting_09_66_111_7502_alt/) | `09 66 111 7502` | HARTING | [cern_harting_09_66_111_7502_alt](library/connector/cern/cern_harting_09_66_111_7502_alt) |
| [09 66 152 6612 (CERN library)](https://partreel.com/p/cern_harting_09_66_152_6612/) | `09 66 152 6612` | HARTING | [cern_harting_09_66_152_6612](library/connector/cern/cern_harting_09_66_152_6612) |
| [09 66 152 6612 (CERN library)](https://partreel.com/p/cern_harting_09_66_152_6612_alt/) | `09 66 152 6612` | HARTING | [cern_harting_09_66_152_6612_alt](library/connector/cern/cern_harting_09_66_152_6612_alt) |
| [09 66 162 6817 (CERN library)](https://partreel.com/p/cern_harting_09_66_162_6817/) | `09 66 162 6817` | HARTING | [cern_harting_09_66_162_6817](library/connector/cern/cern_harting_09_66_162_6817) |
| [09 66 162 6817 (CERN library)](https://partreel.com/p/cern_harting_09_66_162_6817_alt/) | `09 66 162 6817` | HARTING | [cern_harting_09_66_162_6817_alt](library/connector/cern/cern_harting_09_66_162_6817_alt) |
| [09 66 252 6612 (CERN library)](https://partreel.com/p/cern_harting_09_66_252_6612/) | `09 66 252 6612` | HARTING | [cern_harting_09_66_252_6612](library/connector/cern/cern_harting_09_66_252_6612) |
| [09 66 252 6612 (CERN library)](https://partreel.com/p/cern_harting_09_66_252_6612_alt/) | `09 66 252 6612` | HARTING | [cern_harting_09_66_252_6612_alt](library/connector/cern/cern_harting_09_66_252_6612_alt) |
| [09 66 252 7611 (CERN library)](https://partreel.com/p/cern_harting_09_66_252_7611/) | `09 66 252 7611` | HARTING | [cern_harting_09_66_252_7611](library/connector/cern/cern_harting_09_66_252_7611) |
| [09 66 252 7611 (CERN library)](https://partreel.com/p/cern_harting_09_66_252_7611_alt/) | `09 66 252 7611` | HARTING | [cern_harting_09_66_252_7611_alt](library/connector/cern/cern_harting_09_66_252_7611_alt) |
| [09 66 311 7502 (CERN library)](https://partreel.com/p/cern_harting_09_66_311_7502/) | `09 66 311 7502` | HARTING | [cern_harting_09_66_311_7502](library/connector/cern/cern_harting_09_66_311_7502) |
| [09 66 311 7502 (CERN library)](https://partreel.com/p/cern_harting_09_66_311_7502_alt/) | `09 66 311 7502` | HARTING | [cern_harting_09_66_311_7502_alt](library/connector/cern/cern_harting_09_66_311_7502_alt) |
| [09 66 312 7601 (CERN library)](https://partreel.com/p/cern_harting_09_66_312_7601/) | `09 66 312 7601` | HARTING | [cern_harting_09_66_312_7601](library/connector/cern/cern_harting_09_66_312_7601) |
| [09 66 312 7601 (CERN library)](https://partreel.com/p/cern_harting_09_66_312_7601_alt/) | `09 66 312 7601` | HARTING | [cern_harting_09_66_312_7601_alt](library/connector/cern/cern_harting_09_66_312_7601_alt) |
| [09 66 351 6512 (CERN library)](https://partreel.com/p/cern_harting_09_66_351_6512/) | `09 66 351 6512` | HARTING | [cern_harting_09_66_351_6512](library/connector/cern/cern_harting_09_66_351_6512) |
| [09 66 351 6512 (CERN library)](https://partreel.com/p/cern_harting_09_66_351_6512_alt/) | `09 66 351 6512` | HARTING | [cern_harting_09_66_351_6512_alt](library/connector/cern/cern_harting_09_66_351_6512_alt) |
| [09 66 411 7502 (CERN library)](https://partreel.com/p/cern_harting_09_66_411_7502/) | `09 66 411 7502` | HARTING | [cern_harting_09_66_411_7502](library/connector/cern/cern_harting_09_66_411_7502) |
| [09 66 411 7502 (CERN library)](https://partreel.com/p/cern_harting_09_66_411_7502_alt/) | `09 66 411 7502` | HARTING | [cern_harting_09_66_411_7502_alt](library/connector/cern/cern_harting_09_66_411_7502_alt) |
| [09 66 452 6612 (CERN library)](https://partreel.com/p/cern_harting_09_66_452_6612/) | `09 66 452 6612` | HARTING | [cern_harting_09_66_452_6612](library/connector/cern/cern_harting_09_66_452_6612) |
| [09 66 452 6612 (CERN library)](https://partreel.com/p/cern_harting_09_66_452_6612_alt/) | `09 66 452 6612` | HARTING | [cern_harting_09_66_452_6612_alt](library/connector/cern/cern_harting_09_66_452_6612_alt) |
| [09 66 511 6502 (CERN library)](https://partreel.com/p/cern_harting_09_66_511_6502/) | `09 66 511 6502` | HARTING | [cern_harting_09_66_511_6502](library/connector/cern/cern_harting_09_66_511_6502) |
| [09 66 511 6502 (CERN library)](https://partreel.com/p/cern_harting_09_66_511_6502_alt/) | `09 66 511 6502` | HARTING | [cern_harting_09_66_511_6502_alt](library/connector/cern/cern_harting_09_66_511_6502_alt) |
| [09 66 521 6702 (CERN library)](https://partreel.com/p/cern_harting_09_66_521_6702/) | `09 66 521 6702` | HARTING | [cern_harting_09_66_521_6702](library/connector/cern/cern_harting_09_66_521_6702) |
| [09 66 521 6702 (CERN library)](https://partreel.com/p/cern_harting_09_66_521_6702_alt/) | `09 66 521 6702` | HARTING | [cern_harting_09_66_521_6702_alt](library/connector/cern/cern_harting_09_66_521_6702_alt) |
| [09 66 552 7611 (CERN library)](https://partreel.com/p/cern_harting_09_66_552_7611/) | `09 66 552 7611` | HARTING | [cern_harting_09_66_552_7611](library/connector/cern/cern_harting_09_66_552_7611) |
| [09 66 552 7611 (CERN library)](https://partreel.com/p/cern_harting_09_66_552_7611_alt/) | `09 66 552 7611` | HARTING | [cern_harting_09_66_552_7611_alt](library/connector/cern/cern_harting_09_66_552_7611_alt) |
| [09 66 562 7811 (CERN library)](https://partreel.com/p/cern_harting_09_66_562_7811/) | `09 66 562 7811` | HARTING | [cern_harting_09_66_562_7811](library/connector/cern/cern_harting_09_66_562_7811) |
| [09 66 562 7811 (CERN library)](https://partreel.com/p/cern_harting_09_66_562_7811_alt/) | `09 66 562 7811` | HARTING | [cern_harting_09_66_562_7811_alt](library/connector/cern/cern_harting_09_66_562_7811_alt) |
| [09 67 009 4754 (CERN library)](https://partreel.com/p/cern_harting_09_67_009_4754/) | `09 67 009 4754` | HARTING | [cern_harting_09_67_009_4754](library/connector/cern/cern_harting_09_67_009_4754) |
| [09 67 009 4754 (CERN library)](https://partreel.com/p/cern_harting_09_67_009_4754_alt/) | `09 67 009 4754` | HARTING | [cern_harting_09_67_009_4754_alt](library/connector/cern/cern_harting_09_67_009_4754_alt) |
| [09 67 015 4707 (CERN library)](https://partreel.com/p/cern_harting_09_67_015_4707/) | `09 67 015 4707` | HARTING | [cern_harting_09_67_015_4707](library/connector/cern/cern_harting_09_67_015_4707) |
| [09 67 015 4707 (CERN library)](https://partreel.com/p/cern_harting_09_67_015_4707_alt/) | `09 67 015 4707` | HARTING | [cern_harting_09_67_015_4707_alt](library/connector/cern/cern_harting_09_67_015_4707_alt) |
| [09 67 015 4754 (CERN library)](https://partreel.com/p/cern_harting_09_67_015_4754/) | `09 67 015 4754` | HARTING | [cern_harting_09_67_015_4754](library/connector/cern/cern_harting_09_67_015_4754) |
| [09 67 015 4754 (CERN library)](https://partreel.com/p/cern_harting_09_67_015_4754_a/) | `09 67 015 4754` | HARTING | [cern_harting_09_67_015_4754_a](library/connector/cern/cern_harting_09_67_015_4754_a) |
| [09 67 015 4754 (CERN library)](https://partreel.com/p/cern_harting_09_67_015_4754_a_alt/) | `09 67 015 4754` | HARTING | [cern_harting_09_67_015_4754_a_alt](library/connector/cern/cern_harting_09_67_015_4754_a_alt) |
| [09 67 015 4754 (CERN library)](https://partreel.com/p/cern_harting_09_67_015_4754_alt/) | `09 67 015 4754` | HARTING | [cern_harting_09_67_015_4754_alt](library/connector/cern/cern_harting_09_67_015_4754_alt) |
| [09 67 015 5654 (CERN library)](https://partreel.com/p/cern_harting_09_67_015_5654/) | `09 67 015 5654` | HARTING | [cern_harting_09_67_015_5654](library/connector/cern/cern_harting_09_67_015_5654) |
| [09 67 015 5654 (CERN library)](https://partreel.com/p/cern_harting_09_67_015_5654_a/) | `09 67 015 5654` | HARTING | [cern_harting_09_67_015_5654_a](library/connector/cern/cern_harting_09_67_015_5654_a) |
| [09 67 015 5654 (CERN library)](https://partreel.com/p/cern_harting_09_67_015_5654_a_alt/) | `09 67 015 5654` | HARTING | [cern_harting_09_67_015_5654_a_alt](library/connector/cern/cern_harting_09_67_015_5654_a_alt) |
| [09 67 015 5654 (CERN library)](https://partreel.com/p/cern_harting_09_67_015_5654_alt/) | `09 67 015 5654` | HARTING | [cern_harting_09_67_015_5654_alt](library/connector/cern/cern_harting_09_67_015_5654_alt) |
| [09 67 025 4755 (CERN library)](https://partreel.com/p/cern_harting_09_67_025_4755/) | `09 67 025 4755` | HARTING | [cern_harting_09_67_025_4755](library/connector/cern/cern_harting_09_67_025_4755) |
| [09 67 025 4755 (CERN library)](https://partreel.com/p/cern_harting_09_67_025_4755_a/) | `09 67 025 4755` | HARTING | [cern_harting_09_67_025_4755_a](library/connector/cern/cern_harting_09_67_025_4755_a) |
| [09 67 025 4755 (CERN library)](https://partreel.com/p/cern_harting_09_67_025_4755_a_alt/) | `09 67 025 4755` | HARTING | [cern_harting_09_67_025_4755_a_alt](library/connector/cern/cern_harting_09_67_025_4755_a_alt) |
| [09 67 025 4755 (CERN library)](https://partreel.com/p/cern_harting_09_67_025_4755_alt/) | `09 67 025 4755` | HARTING | [cern_harting_09_67_025_4755_alt](library/connector/cern/cern_harting_09_67_025_4755_alt) |
| [09 67 025 5655 (CERN library)](https://partreel.com/p/cern_harting_09_67_025_5655/) | `09 67 025 5655` | HARTING | [cern_harting_09_67_025_5655](library/connector/cern/cern_harting_09_67_025_5655) |
| [09 67 025 5655 (CERN library)](https://partreel.com/p/cern_harting_09_67_025_5655_a/) | `09 67 025 5655` | HARTING | [cern_harting_09_67_025_5655_a](library/connector/cern/cern_harting_09_67_025_5655_a) |
| [09 67 025 5655 (CERN library)](https://partreel.com/p/cern_harting_09_67_025_5655_a_alt/) | `09 67 025 5655` | HARTING | [cern_harting_09_67_025_5655_a_alt](library/connector/cern/cern_harting_09_67_025_5655_a_alt) |
| [09 67 025 5655 (CERN library)](https://partreel.com/p/cern_harting_09_67_025_5655_alt/) | `09 67 025 5655` | HARTING | [cern_harting_09_67_025_5655_alt](library/connector/cern/cern_harting_09_67_025_5655_alt) |
| [09 67 037 4754 (CERN library)](https://partreel.com/p/cern_harting_09_67_037_4754/) | `09 67 037 4754` | HARTING | [cern_harting_09_67_037_4754](library/connector/cern/cern_harting_09_67_037_4754) |
| [09 67 037 4754 (CERN library)](https://partreel.com/p/cern_harting_09_67_037_4754_alt/) | `09 67 037 4754` | HARTING | [cern_harting_09_67_037_4754_alt](library/connector/cern/cern_harting_09_67_037_4754_alt) |
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
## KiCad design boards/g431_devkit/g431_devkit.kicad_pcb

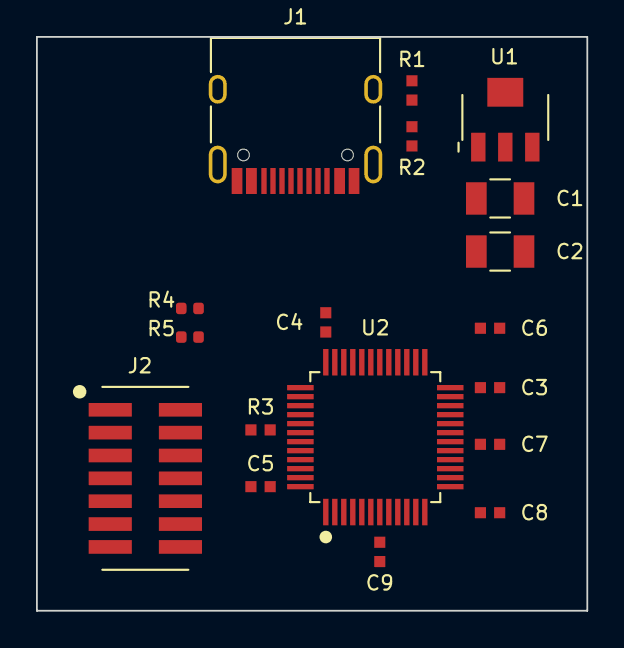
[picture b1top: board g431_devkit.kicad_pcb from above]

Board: 2 copper layers, 30.6 x 31.9 mm, 18 parts (0 on the bottom side), 16 nets, no tracks yet.

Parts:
C1, C2: VAL**; antmicro_c3216x7r1h106k160ae
C3, C4, C5, C7, C9: VAL**; antmicro_cl05a104ka5nnnc
C6: VAL**; antmicro_cl05a475kq5nrnc
C8: VAL**; samsung_cl05a105ka5nnnc
J1: usb_c_16p
J2: samtec_ftsh_107_01_l_dv_k
R1, R2: VAL**; vishay_crcw04025k10fked
R3: VAL**; vishay_crcw040210k0fked
R4, R5: R_0402_1005Metric; antmicro_crcw04021k80fkedc
U1: ht7333
U2: VAL**; stm32g431cbtx

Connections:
+3V3: C2.2, C3.2, C4.2, C5.2, C6.2, C7.2, C8.2, J2.3, R4.2, R5.2, U1.3, U2.1, U2.20, U2.21, U2.24, U2.36, U2.48
+5V: C1.2, J1.A4, J1.A9, J1.B4, J1.B9, U1.2
GND: C1.1, C2.1, C3.1, C4.1, C5.1, C6.1, C7.1, C8.1, C9.1, J1.A1, J1.A12, J1.B1, J1.B12, J1.S1, J2.5, J2.7, J2.11, R1.1, R2.1, R3.2, U1.1, U2.19, U2.23, U2.35, U2.47
NRST: C9.2, J2.12, U2.7
unnamed: J1.A5, R1.2
unnamed: J1.B5, R2.2
unnamed: R3.1, U2.45
SCL: R5.1, U2.39
SDA: R4.1, U2.44
SWCLK: J2.6, U2.38
SWDIO: J2.4, U2.37
SWO: J2.8, U2.40
UART_RX: J2.13, U2.11
UART_TX: J2.14, U2.10
USB_DM: J1.A7, J1.B7, U2.33
USB_DP: J1.A6, J1.B6, U2.34

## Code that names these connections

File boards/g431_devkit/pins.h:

/* pins.h — generated by build_board.py from boards/g431_devkit/board.json
 * rev 0.3 — DO NOT EDIT (source: board.json)
 */
#ifndef PARTREEL_PINS_H
#define PARTREEL_PINS_H

#define SCL_GPIO_Port GPIOA
#define SCL_Pin GPIO_PIN_15
#define SDA_GPIO_Port GPIOB
#define SDA_Pin GPIO_PIN_7
#define SWO_GPIO_Port GPIOB
#define SWO_Pin GPIO_PIN_3
#define UART_RX_GPIO_Port GPIOA
#define UART_RX_Pin GPIO_PIN_3
#define UART_TX_GPIO_Port GPIOA
#define UART_TX_Pin GPIO_PIN_2
#define USB_DM_GPIO_Port GPIOA
#define USB_DM_Pin GPIO_PIN_11
#define USB_DP_GPIO_Port GPIOA
#define USB_DP_Pin GPIO_PIN_12

#endif /* PARTREEL_PINS_H */

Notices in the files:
parts and their libraries:
License: Apache-2.0
